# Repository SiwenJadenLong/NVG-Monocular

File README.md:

# NVG-Monocular
A night vision monocular based on the PVS-69 Night Vision System

I wanted to practice more with PCB design, so I'm making this upgrade to my current usb-c powered night vision monocular.

### Minimal things needed:
- Somewhat small 1 Cell Charging and protection circuit
- 5V output for the Display and Camera
- 1000 mAh battery

### Things I'd Like, in order:
1. able to take and hotswap standard 18650 Cells
2. Fuel Gauge and auto shutoff at 3.2v
3. Oled Display displaying battery life
4. small buttons for camera settings

Current Hardware (11/24):
-RunCam Night Eagle v2
-What I think is a V760 Display Assembly

Plan (12/26/25):
1. (We are here!) Create Breakout board for MP2696A battery charging boast monitor combo circuit
2. Write Arduino library for MP2696A
3. test and tweak until operational MP2696A circuit with STM32 Nucleo
4. Integrate little aliexpress Oled
5. Create final combo pcb with STM32 embedded
6. Create housing with hot swappable 18650
7. Profit?

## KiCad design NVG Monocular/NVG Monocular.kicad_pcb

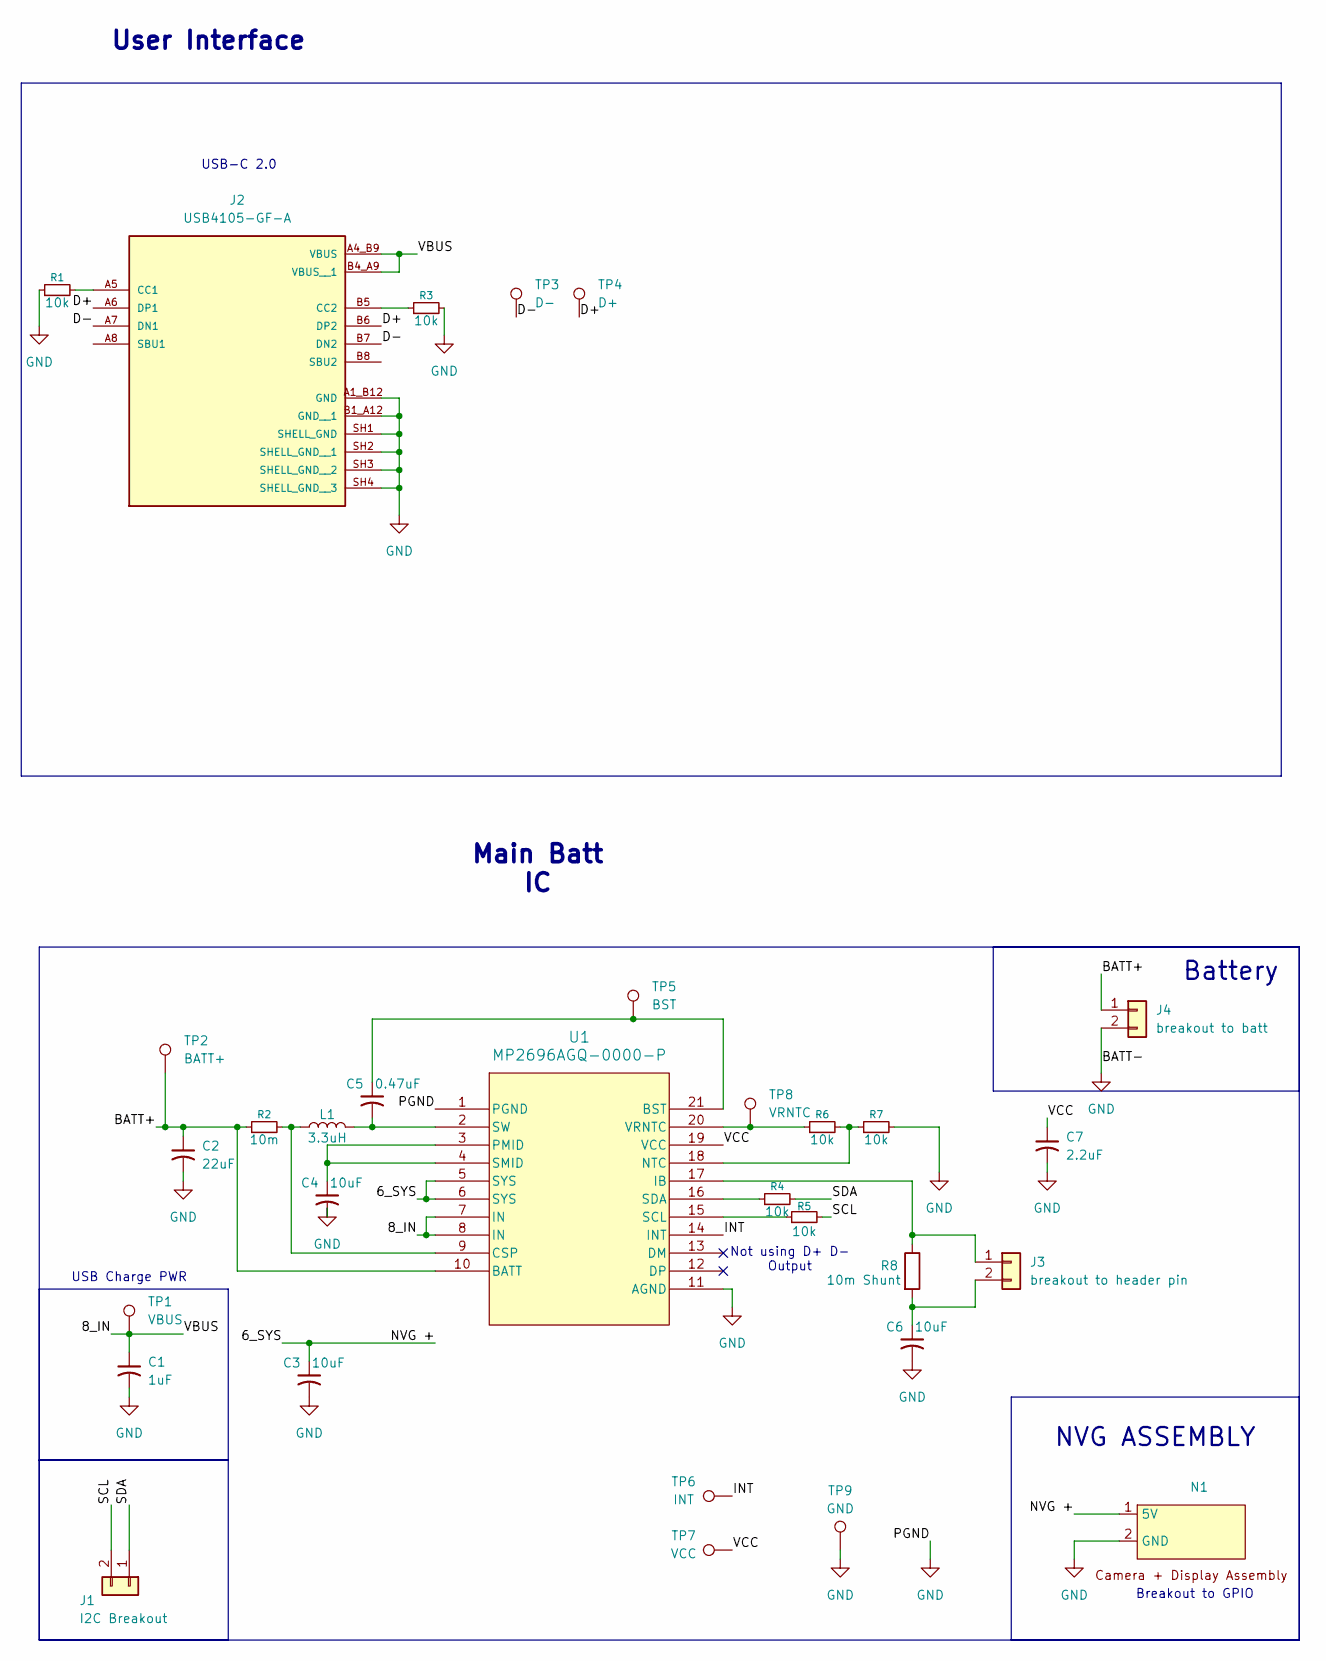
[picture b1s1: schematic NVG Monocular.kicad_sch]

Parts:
C1: 1uF; C_0603_1608Metric_Pad1.08x0.95mm_HandSolder
C2: 22uF; C_0603_1608Metric_Pad1.08x0.95mm_HandSolder
C3, C4, C6: 10uF; C_0805_2012Metric_Pad1.18x1.45mm_HandSolder
C5: 0.47uF; C_0603_1608Metric_Pad1.08x0.95mm_HandSolder
C7: 2.2uF; C_0603_1608Metric_Pad1.08x0.95mm_HandSolder
J1: I2C Breakout; PinHeader_1x02_P1.00mm_Vertical
J2: USB4105-GF-A; GCT_USB4105-GF-A; PARTREV B4
J3: breakout to header pin; PinHeader_1x02_P1.00mm_Vertical
J4: breakout to batt; PinHeader_1x02_P1.00mm_Vertical
L1: 3.3uH; IND_IHLM-2525CZ_VIS
N1: PinHeader_1x02_P1.00mm_Vertical
R1, R3, R4, R5, R6, R7: 10k; R_0603_1608Metric
R2: 10m; R_1206_3216Metric_Pad1.30x1.75mm_HandSolder
R8: 10m Shunt; R_0603_1608Metric_Pad0.98x0.95mm_HandSolder
TP1: VBUS; TestPoint_Pad_D1.5mm
TP2: BATT+; TestPoint_Pad_D1.5mm
TP3: D-; TestPoint_Pad_D1.5mm
TP4: D+; TestPoint_Pad_D1.5mm
TP5: BST; TestPoint_Pad_D1.5mm
TP6: INT; TestPoint_Pad_D1.5mm
TP7: VCC; TestPoint_Pad_D1.5mm
TP8: VRNTC; TestPoint_Pad_D1.5mm
TP9: GND; TestPoint_Pad_D1.5mm
U1: MP2696AGQ-0000-P; QFN21_3MMx3MM_MNP

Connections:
/6_SYS: C3.1, N1.1 (5V), U1.5 (SYS), U1.6 (SYS)
/8_IN: C1.1, J2.A4_B9 (VBUS), J2.B4_A9 (VBUS__1), TP1.1, U1.7 (IN), U1.8 (IN)
/BATT+: C2.1, J4.1, R2.1, TP2.1, U1.10 (BATT)
/D+: J2.A6 (DP1), J2.B6 (DP2), TP4.1
/D-: J2.A7 (DN1), J2.B7 (DN2), TP3.1
/INT: TP6.1, U1.14 (INT)
/SCL: J1.2, R5.2
/SDA: J1.1, R4.2
/VCC: C7.1, TP7.1, U1.19 (VCC)
GND: C1.2, C2.2, C3.2, C4.2, C6.2, C7.2, J2.A1_B12 (GND), J2.B1_A12 (GND__1), J2.SH1 (SHELL_GND), J2.SH2 (SHELL_GND__1), J2.SH3 (SHELL_GND__2), J2.SH4 (SHELL_GND__3), J4.2, N1.2 (GND), R1.1, R3.2, R7.2, TP9.1, U1.1 (PGND), U1.11 (AGND)
unnamed: J2.A5 (CC1), R1.2
unnamed: J2.B5 (CC2), R3.1
unnamed: J3.1, R8.1, U1.17 (IB)
unnamed: C6.1, J3.2, R8.2
unnamed: C5.1, TP5.1, U1.21 (BST)
unnamed: L1.1, R2.2, U1.9 (CSP)
unnamed: R6.2, R7.1, U1.18 (NTC)
unnamed: C4.1, U1.3 (PMID), U1.4 (SMID)
unnamed: R5.1, U1.15 (SCL)
unnamed: R4.1, U1.16 (SDA)
unnamed: C5.2, L1.2, U1.2 (SW)
unnamed: R6.1, TP8.1, U1.20 (VRNTC)

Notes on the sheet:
USB Charge PWR
Not using D+ D- Output
Breakout to GPIO
USB-C 2.0
Battery
User Interface
Main Batt IC
NVG ASSEMBLY

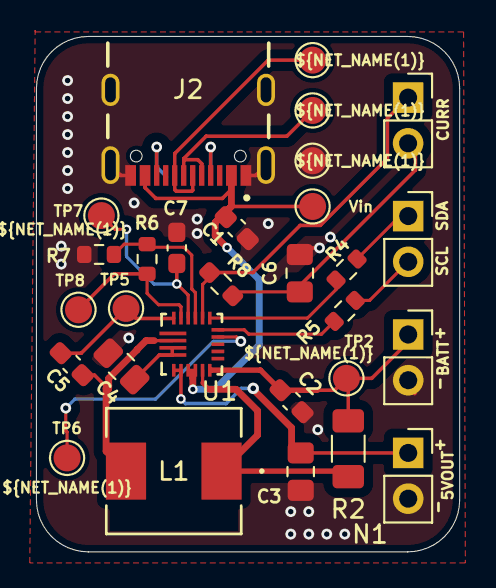
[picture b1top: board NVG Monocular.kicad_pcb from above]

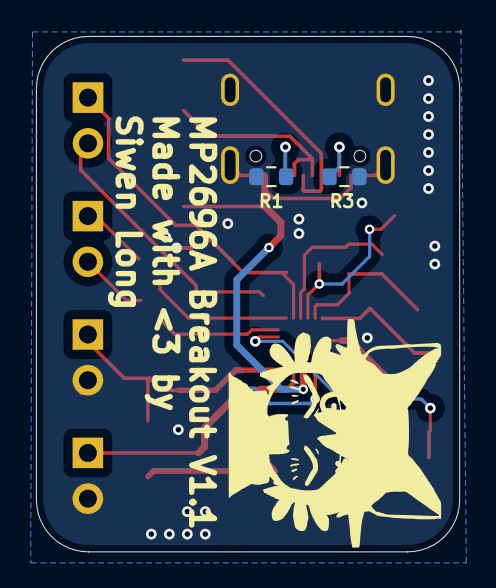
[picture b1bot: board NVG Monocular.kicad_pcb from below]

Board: 2 copper layers, 23.5 x 28.6 mm, 31 parts (2 on the bottom side), 22 nets.

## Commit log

2025-11-25 Initial README.md
2025-11-27 Drew MP2696AGQ general Passives
2025-11-27 Added USB-C and speced out Charge IC passives
2025-12-25 Schematic ready for layout
2025-12-25 layout partialy finished, some test points removed
2025-12-26 V1 breakout completed and ordered
2026-01-09 updated readme and fixed 3D models
2026-01-12 V1.1 Corrected Header size to 2.54mm
